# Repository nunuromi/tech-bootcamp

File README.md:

# tech-bootcamp

## BOOTCAMP TECNOLÓGICO

Nuestro bootcamp está indicado para jóvenes entre 12 y 16 años con curiosidad por la tecnología e inquietud por fabricar su propio mundo.

Se trata de un Bootcamp Tecnológico único en León, y uno de los pocos a nivel nacional y mundial.
Fechas: del 29 de Junio al 3 de Julio
Horario: de 09:00 a 14:00
Edades recomendada: de 12 a 16 años.
Precio: 50€ de matrícula + 295€ Curso
 
El curso incluye:
* Aprendizaje y uso de las herramientas de fabricación digital de Fab Lab León. (Impresión 3D, Corte láser, Ploter de corte...)
* Kit de electrónica con Arduino.
* Mentorización de los proyectos finales de los alumnos por instructores reconocidos mundialmente en la red de Fab Labs.
	
## IMPRESIÓN 3D

Esta tecnología está ahora mismo en la punta de lanza de todas las que engloban la fabricación digital. Las empresas ya consideran esta skill como algo fundamental en sus departamentos de I+D+I de cualquier especialidad o rama industrial.
Aprenderán a diseñar, preparar ficheros e imprimir durante este bootcamp, dando alas a su capacidad de fabricación.

## CORTE LÁSER

Esta tecnología está presente en cualquier industria, pero aún no ha llegado de forma accesible al usuario final. La producción mediante esta tecnología es miles de veces más rápida que otras como la impresión 3D, pero hay que saber diseñar para fabricar objetos mediante corte láser.
Aprenderán a diseñar y fabricar objetos mediante esta tecnología.

## ARDUINO

La electrónica es mucho más accesible desde la aparición de la plataforma Arduino, un conjunto de herramientas que nos permite controlar motores, sensores y hacer que nuestros proyectos interaccionen con las personas.
Aprenderán a usar, controlar y desarrollar sus propios proyectos, desde la ropa inteligente (wearable) a robótica, maquinas CNC e Internet de las cosas. El futuro sólo se entiende si entendemos la electrónica que nos rodea.
Y MUCHO MÁS...

Programación | Plotter de corte | Páginas web | Documentación |Proyectos propios...

### Y LO MÁS IMPORTANTE
Damos una formación personalizada y siempre tratando de potenciar otras habilidades menos técnicas, pero igual de importantes para nosotros, como la comunicación, el trabajo en equipo, la resolución de problemas...

Favorecemos la mejora de skills no tecnológicos a través de nuestra forma de trasladar nuestros conocimientos.

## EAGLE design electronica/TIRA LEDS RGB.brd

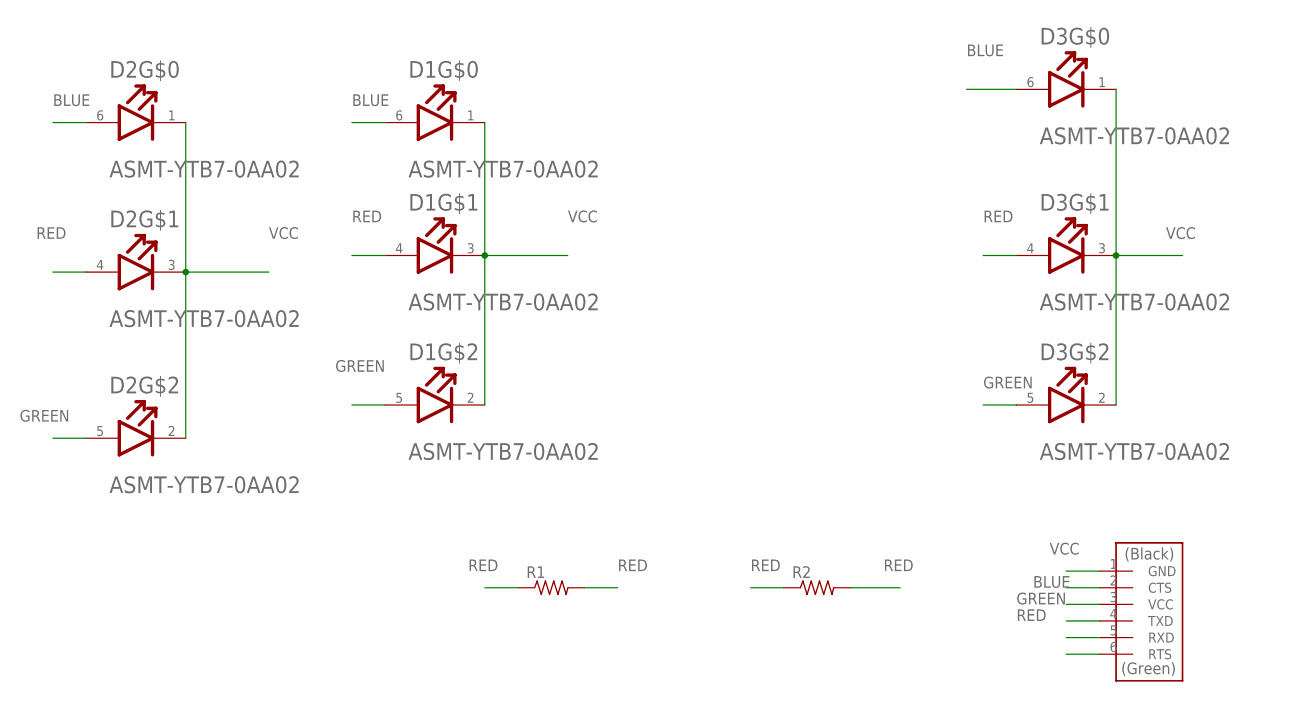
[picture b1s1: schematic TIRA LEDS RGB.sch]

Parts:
D1, D2, D3: BROADCOM_ASMT-YTB7-0AA02BROADCOM_ASMT-YTB7-0AA02_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; BROADCOM_ASMT-YTB7-0AA02_0
R1, R2: R1206FAB
U$1: CONN_06_FTDI-SMD-HEADER; 1X06SMD

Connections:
BLUE: D1.6 (ANODE(BLUE)), D2.6 (ANODE(BLUE)), D3.6 (ANODE(BLUE)), U$1.2 (CTS)
GREEN: D1.5 (ANODE(GREEN)), D2.5 (ANODE(GREEN)), D3.5 (ANODE(GREEN)), U$1.3 (VCC)
RED: D1.4 (ANODE(RED)), D2.4 (ANODE(RED)), D3.4 (ANODE(RED)), R1.1, R1.2, R2.1, R2.2, U$1.4 (TXD)
VCC: D1.1 (CATHODE(BLUE)), D1.2 (CATHODE(GREEN)), D1.3 (CATHODE(RED)), D2.1 (CATHODE(BLUE)), D2.2 (CATHODE(GREEN)), D2.3 (CATHODE(RED)), D3.1 (CATHODE(BLUE)), D3.2 (CATHODE(GREEN)), D3.3 (CATHODE(RED)), U$1.1 (GND)

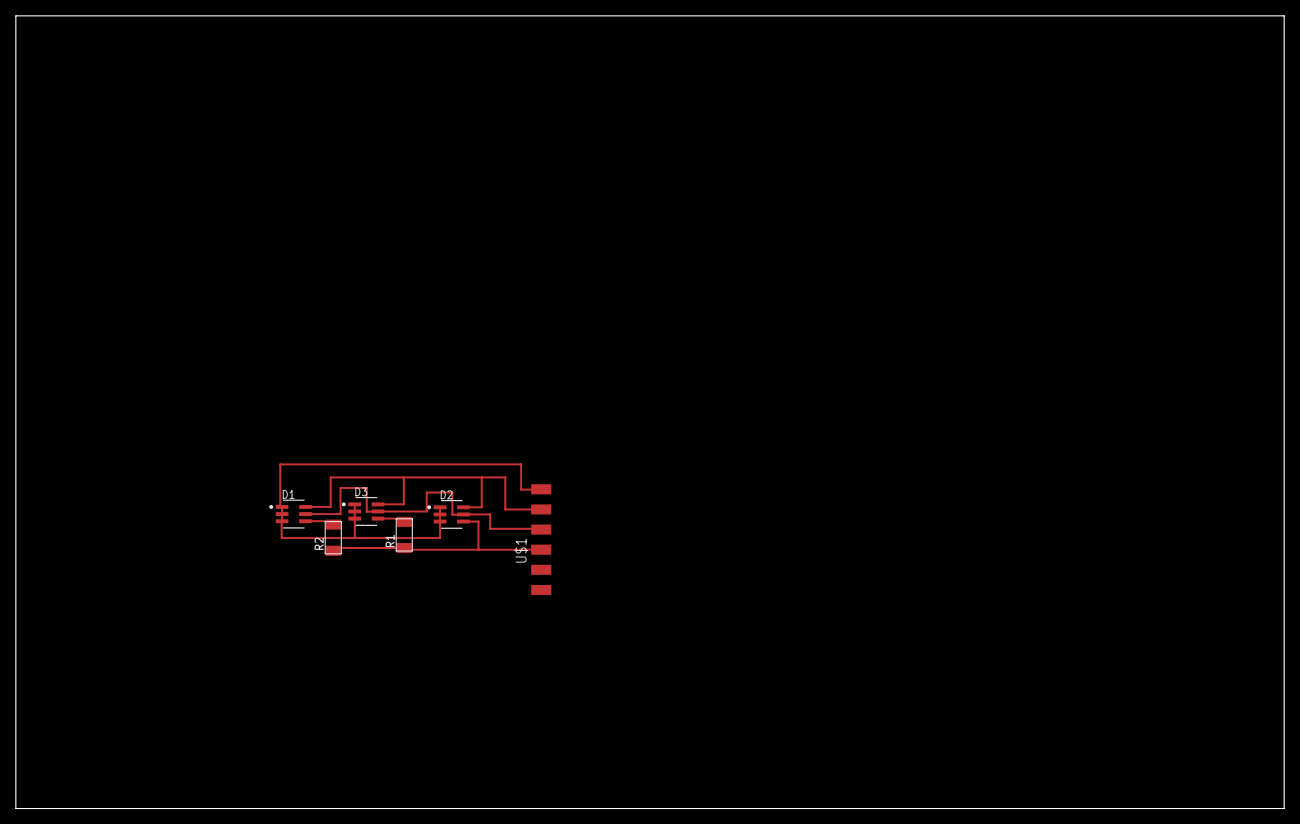
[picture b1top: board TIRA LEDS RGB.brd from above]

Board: 2 copper layers, 160.0 x 100.0 mm, 6 parts (0 on the bottom side), 4 nets.

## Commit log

2020-06-14 Create pot-neopixel
2020-06-14 Create introduccion
2020-06-14 Update introduccion
2020-06-14 Update pot-neopixel
